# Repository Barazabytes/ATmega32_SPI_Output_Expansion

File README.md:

# ATmega32 SPI Output Expansion

## Overview

This project demonstrates SPI-based output expansion using the ATmega32 microcontroller. The system utilizes the Serial Peripheral Interface (SPI) protocol to control multiple output devices through external expansion hardware. The project includes firmware development, hardware design files, simulation resources, technical documentation, and demonstration media.

The repository is organized to support embedded systems development workflows including firmware programming, PCB design, simulation, testing, and documentation.

---

# Project Structure

```text
ATmega32_SPI_Output_Expansion/
│
├── README.md
│
├── firmware/
│   ├── src/
│   ├── include/
│   └── hex/
│
├── kicad/
│   ├── schematic/
│   ├── pcb/
│   └── gerber/
│
├── simulide/
│   ├── circuit/
│   └── screenshots/
│
├── documentation/
│   ├── block_diagram.png
│   ├── flowchart.png
│   ├── spi_configuration.md
│   ├── pin_mapping_table.md
│   └── test_results.md
│
└── media/
    └── demonstration_video_link.txt
```

---

# Directory Description

## `firmware/`

Contains all embedded software files for the ATmega32 microcontroller.

### `src/`

Stores source code files such as:

* `main.c`
* SPI driver implementation
* Peripheral control logic

### `include/`

Contains header files:

* Register definitions
* Function prototypes
* Macro definitions
* Configuration files

### `hex/`

Compiled firmware output files:

* `.hex`
* `.elf`
* Binary images ready for flashing

---

## `kicad/`

Contains hardware design resources created using KiCad.

### `schematic/`

Circuit schematic files:

* `.kicad_sch`
* PDF schematic exports

### `pcb/`

PCB layout design files:

* Board routing
* Component placement
* PCB design assets

### `gerber/`

Manufacturing-ready Gerber files:

* Copper layers
* Silkscreen
* Drill files
* Fabrication outputs

---

## `simulide/`

Simulation resources for testing and demonstration.

### `circuit/`

SimulIDE project files and circuit simulations.

### `screenshots/`

Images captured from simulation runs and testing.

---

## `documentation/`

Technical documentation and supporting project materials.

### `block_diagram.png`

High-level system architecture diagram.

### `flowchart.png`

Program execution and logic flow representation.

### `spi_configuration.md`

Detailed explanation of SPI setup and register configuration.

### `pin_mapping_table.md`

ATmega32 pin assignments and external device connections.

### `test_results.md`

System testing observations, validation results, and performance analysis.

---

## `media/`

Stores demonstration and presentation resources.

### `demonstration_video_link.txt`

Contains the link to the project demonstration video.

---

# Features

* SPI communication using ATmega32
* Output expansion through serial interface
* Embedded C firmware development
* Hardware schematic and PCB design
* Simulation support using SimulIDE
* Technical documentation and testing resources

---

# Tools and Technologies

* ATmega32 Microcontroller
* AVR-GCC
* KiCad
* SimulIDE
* Embedded C
* SPI Protocol

---

# Applications

This project can be used for:

* GPIO expansion
* LED matrix control
* Embedded systems learning
* Peripheral interfacing
* Industrial output control systems
* Educational laboratory demonstrations

---

# Author

Developed as an embedded systems and SPI communication project using the ATmega32 microcontroller platform.

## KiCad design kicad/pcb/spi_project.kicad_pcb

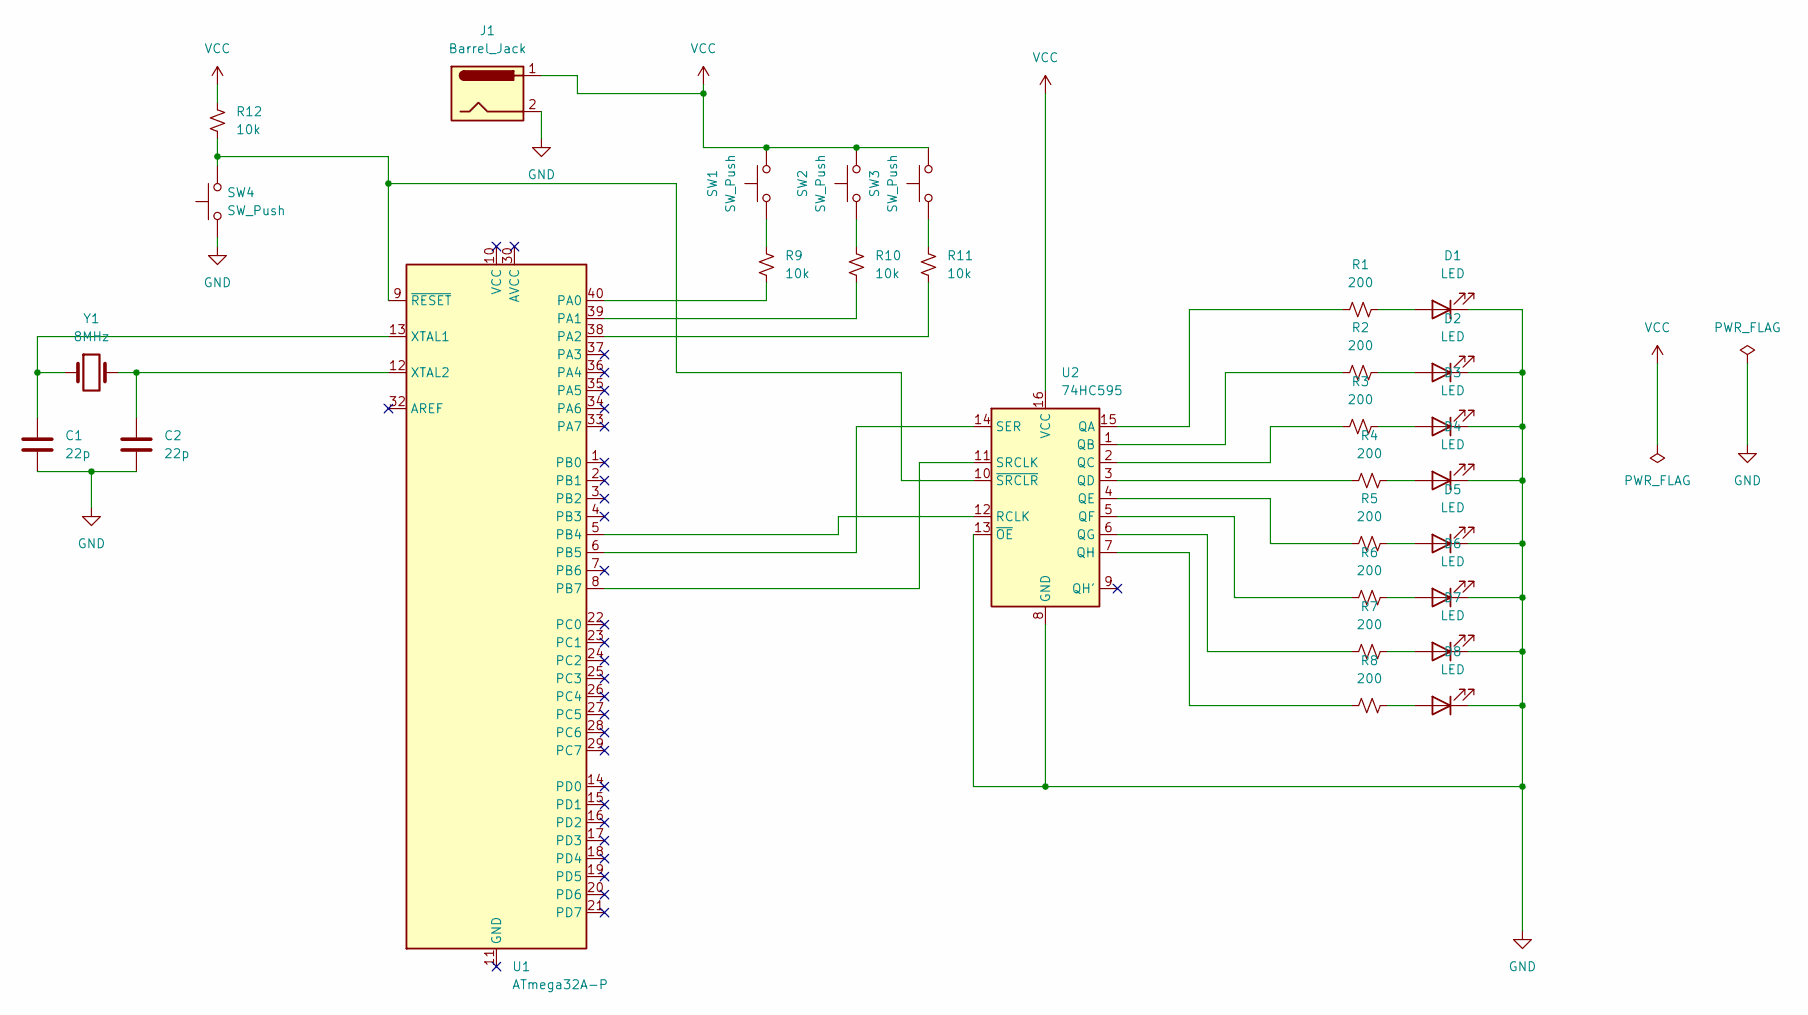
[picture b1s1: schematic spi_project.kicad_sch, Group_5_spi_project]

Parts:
C1, C2: 22p; C_Disc_D3.0mm_W1.6mm_P2.50mm
D1, D2, D3, D4, D5, D6, D7, D8: LED; LED_D3.0mm
J1: Barrel_Jack; BarrelJack_GCT_DCJ200-10-A_Horizontal
R1, R2, R3, R4, R5, R6, R7, R8: 200; R_Axial_DIN0204_L3.6mm_D1.6mm_P7.62mm_Horizontal
R9, R10, R11, R12: 10k; R_Axial_DIN0204_L3.6mm_D1.6mm_P7.62mm_Horizontal
SW1, SW2, SW3, SW4: SW_Push; SW_PUSH_6mm
U1: ATmega32A-P; DIP-40_W15.24mm
U2: 74HC595; DIP-16_W7.62mm
Y1: 8MHz; Crystal_HC49-4H_Vertical

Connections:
GND: C1.2, C2.2, D1.1 (K), D2.1 (K), D3.1 (K), D4.1 (K), D5.1 (K), D6.1 (K), D7.1 (K), D8.1 (K), J1.2, SW4.1, U2.8 (GND), U2.13 (~OE)
unnamed: D1.2 (A), R1.2
unnamed: D2.2 (A), R2.2
unnamed: D3.2 (A), R3.2
unnamed: D4.2 (A), R4.2
unnamed: D5.2 (A), R5.2
unnamed: D6.2 (A), R6.2
unnamed: D7.2 (A), R7.2
unnamed: D8.2 (A), R8.2
unnamed: R9.2, SW1.1
unnamed: R10.2, SW2.1
unnamed: R11.2, SW3.1
unnamed: R9.1, U1.40 (PA0)
unnamed: R10.1, U1.39 (PA1)
unnamed: R11.1, U1.38 (PA2)
unnamed: U1.5 (PB4), U2.12 (RCLK)
unnamed: U1.6 (PB5), U2.14 (SER)
unnamed: U1.8 (PB7), U2.11 (SRCLK)
unnamed: C1.1, U1.13 (XTAL1), Y1.1
unnamed: C2.1, U1.12 (XTAL2), Y1.2
unnamed: R12.2, SW4.2, U1.9 (~RESET), U2.10 (~SRCLR)
unnamed: R1.1, U2.15 (QA)
unnamed: R2.1, U2.1 (QB)
unnamed: R3.1, U2.2 (QC)
unnamed: R4.1, U2.3 (QD)
unnamed: R5.1, U2.4 (QE)
unnamed: R6.1, U2.5 (QF)
unnamed: R7.1, U2.6 (QG)
unnamed: R8.1, U2.7 (QH)
VCC: J1.1, R12.1, SW1.2, SW2.2, SW3.2, U2.16 (VCC)

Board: 2 copper layers, 30 parts (0 on the bottom side), 30 nets, no tracks yet.

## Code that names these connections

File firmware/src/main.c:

#define F_CPU 8000000UL   // clock speed = 8 MHz

#include <avr/io.h>
#include <util/delay.h>

// Useful constants
#define LATCH_PIN  PB4   // Latch
#define DATA_PIN   PB5   // DATA
#define CLOCK_PIN  PB7   // CLOCK

#define BUTTON1    PA0   // Sweep LEFT to RIGHT
#define BUTTON2    PA1   // Sweep RIGHT to LEFT
#define BUTTON3    PA2   // Blink all LEDs


// Set up the SPI hardware and the three pins we use to talk to the 74HC595
void setup_spi(void) {
    // Set the three pins we use to talk to the 74HC595 as OUTPUTS
    DDRB |= (1 << DATA_PIN) | (1 << CLOCK_PIN) | (1 << LATCH_PIN);

    // Start with latch pin LOW
    PORTB &= ~(1 << LATCH_PIN);

    // Turn on SPI, set as Master
    SPCR = (1 << SPE) | (1 << MSTR);
}

// Set up the three buttons as INPUTS
void setup_buttons(void) {
    // Clear the bits in DDRA to make these pins INPUTS
    DDRA &= ~((1 << BUTTON1) | (1 << BUTTON2) | (1 << BUTTON3));

    // Make sure internal pull-ups are OFF (we use external pull-downs)
    PORTA &= ~((1 << BUTTON1) | (1 << BUTTON2) | (1 << BUTTON3));
}

// Send a single byte to the 74HC595 via SPI
void send_byte(uint8_t data) {
    SPDR = data;                        // Start sending the byte
    while ((SPSR & (1 << SPIF)) == 0);  // Wait for the byte to finish sending
}


// Tell 74HC595 to release Data.
void pulse_latch(void) {
    PORTB |= (1 << LATCH_PIN);    // LATCH HIGH
    PORTB &= ~(1 << LATCH_PIN);   // LATCH LOW
}

// Show the intended patterns on LED
void show_pattern(uint8_t pattern) {
    send_byte(pattern);
    pulse_latch();
}

// Check if Button is pressed.
uint8_t button_is_pressed(uint8_t button_pin) {
    if (PINA & (1 << button_pin)) {
        return 1;   /* Button is pressed */
    } else {
        return 0;   /* Button is not pressed */
    }
}

// Wait until button is released.
void wait_until_released(void) {
    while (button_is_pressed(BUTTON1) || button_is_pressed(BUTTON2) || button_is_pressed(BUTTON3));
    _delay_ms(20);   // small delay (debounce)
}

// LED Animations..

// Turns LEDs on one at a time, from left to right 
void animation_left_to_right(void) {
    uint8_t pattern = 0b00000000;

    for (uint8_t i = 0; i < 8; i++) {
        pattern = (pattern >> 1) | 0b10000000;  // Turn ON led
        show_pattern(pattern);
        _delay_ms(150);                          // Small delay
    }
}

// Turns LEDs on one at a time, from right to left
void animation_right_to_left(void) {
    uint8_t pattern = 0b00000000;

    for (uint8_t i = 0; i < 8; i++) {
        pattern = (pattern << 1) | 0b00000001;  /* turn on one more LED */
        show_pattern(pattern);
        _delay_ms(150);                          /* wait before next step */
    }
}

// Blinks all 8 LEDs together, 5 times
void animation_blink(void) {
    for (uint8_t i = 0; i < 5; i++) {
        show_pattern(0b11111111);   /* all LEDs ON  */
        _delay_ms(300);
        show_pattern(0b00000000);   /* all LEDs OFF */
        _delay_ms(300);
    }
}


int main(void)
{
    // Run our setup functions.
    setup_spi();
    setup_buttons();

    // Make sure all LEDs start OFF
    show_pattern(0b00000000);

    while (1) {

        if (button_is_pressed(BUTTON1)) {
            show_pattern(0b00000000);   // Turn Off all LED's first.
            wait_until_released();
            animation_left_to_right();
        }
        else if (button_is_pressed(BUTTON2)) {
            show_pattern(0b00000000);
            wait_until_released();
            animation_right_to_left();
        }
        else if (button_is_pressed(BUTTON3)) {
            wait_until_released();
            animation_blink();
        }
    }

    return 0;
}

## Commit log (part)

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2026-06-06 Add project report file structure to README
2026-06-06 Revise README.md with detailed project information
    Expanded the README to include project overview, structure, features, tools, applications, and author information.
2026-06-15 Added SPI master firmware, Added LED pattern control logic and Added simulIDE requirements
2026-06-17 Modifying main.c into a required modularity
2026-06-17 Modifying the .hex file to resemble with main.c
2026-06-18 Adding kiCAD directory
2026-06-18 Adding report
2026-06-24 Modifying the main.c file
    _only that!
2026-06-30 Refactor main.c for better readability and organization
    Refactor main.c to improve readability and organization by consolidating pin definitions and simplifying function names.
2026-06-30 Update firmware hex with new data
    Updated default.hex with new firmware data.
